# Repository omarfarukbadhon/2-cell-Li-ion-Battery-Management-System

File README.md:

# Li-ion Battery Management System
A custom-designed 2-cell Li-ion Battery Management System (BMS), developed with Altium.
Key features include: <br>
✅ Surge protection for increased durability <br>
✅ Reverse polarity protection using MOSFET <br>
✅ LCL filter for precise DC signal conditioning

# 3D view of PCB

# PCB Routing

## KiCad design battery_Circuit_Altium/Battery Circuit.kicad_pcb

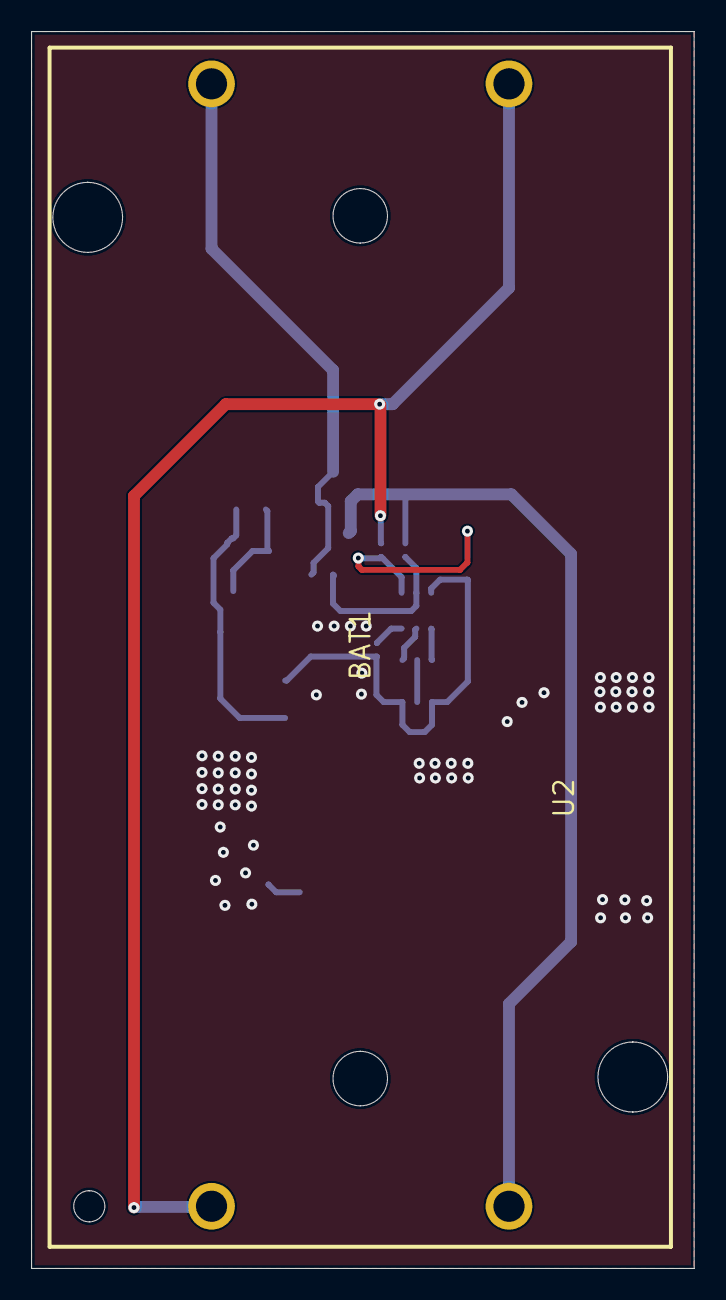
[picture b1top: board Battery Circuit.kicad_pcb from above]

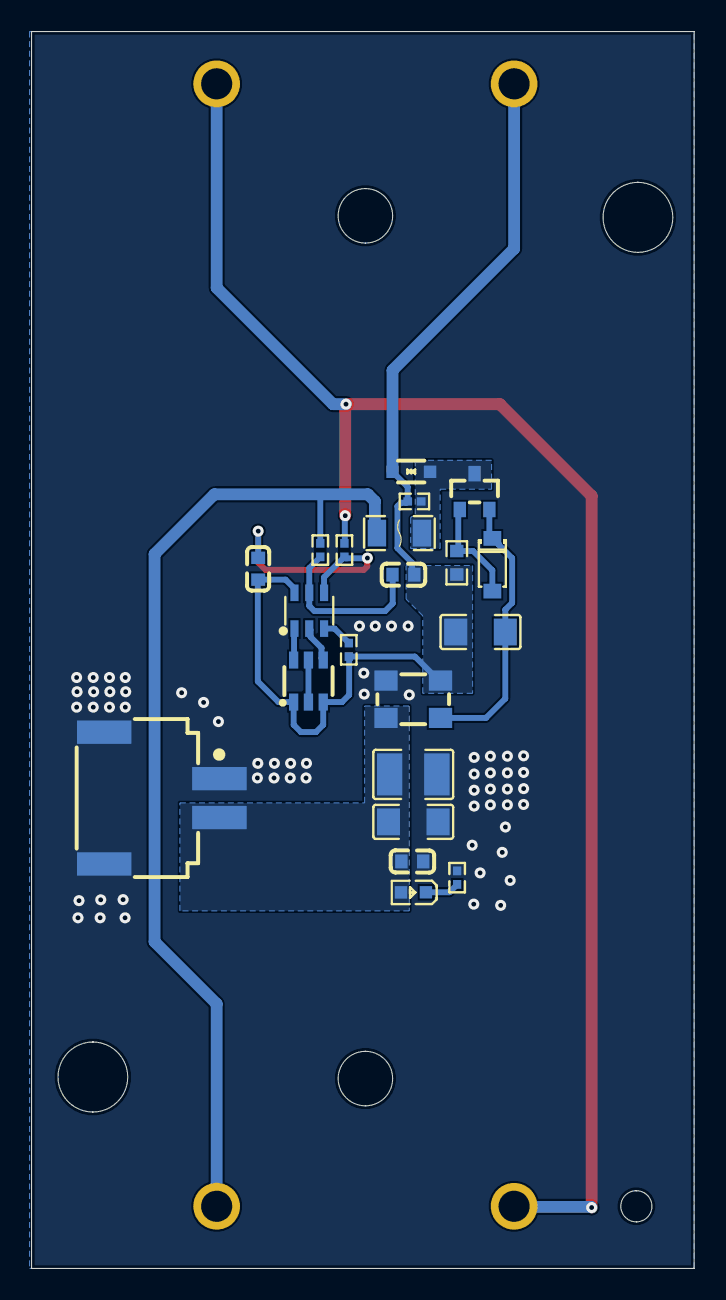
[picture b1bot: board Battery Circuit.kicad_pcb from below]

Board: 2 copper layers, 42.5 x 79.4 mm, 22 parts (21 on the bottom side), 15 nets.

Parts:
BAT1: 2 CELL BATTERY CASE
C1, C2: 47UF CAP
C3: 10UF CAP
C4, C5, C6: 100NF CAP
D1: ZENER DIODE
D2: ESD DIODE
F1: FUSE_2
L1: CMC FILTER
LED1: LED
M1: VARISTOR
Q1: P MOS
Q2: 2 N MOS
R1: 10R RES
R2: 330R RES
R3, R4: 470R RES
R5: 2K RES
U1: BMS
U2: SMD JST 2P

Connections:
BAT+: C2.2, C3.2, C4.2, L1.2, LED1.2, U2.2
Cell_1_N: BAT1.1, BAT1.3, R4.2
Cell_1_P: BAT1.2, F1.1, R3.2
Cell_2_N: BAT1.4, C1.1, C5.1, C6.1, D2.1, L1.4, M1.1, Q2.1, Q2.3, R1.1, R5.1, U1.6
GND: C2.1, C3.1, C4.1, L1.3, R2.1, U2.1, U2.3, U2.4
NetC1_2: C1.2, D1.1, L1.1, Q1.2
NetC5_2: C5.2, R4.1, U1.4
NetC6_2: C6.2, R3.1, U1.5
NetD1_2: D1.2, Q1.1, R1.2
NetD2_2: D2.2, F1.2, M1.2, Q1.3
NetLED1_1: LED1.1, R2.2
NetQ2_2: Q2.2, Q2.5
NetQ2_4: Q2.4, U1.2
NetQ2_6: Q2.6, U1.1
NetR5_2: R5.2, U1.3

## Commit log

2025-05-30 BMS for 2 cell Li-ion battery
2025-05-30 Create README.md
    Add more details
